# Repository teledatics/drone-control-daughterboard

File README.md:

# Drone Control

This is a hardware add-on 'lid' for the kimχ micro that adds drone control hardware
replacing a separate PX4 external embedded subsystem. The kimχ micro with the drone-
control add-on board is an all-in-one embedded drone and rover control system.

The kimχ micro with the drone-control add-on is an [i.MX8M Mini](https://www.nxp.com/products/processors-and-microcontrollers/arm-processors/i-mx-applications-processors/i-mx-8-applications-processors/i-mx-8m-mini-arm-cortex-a53-cortex-m4-audio-voice-video:i.MX8MMINI) Linux system with a 
32mm x 65mm x 10mm form factor.

## kimχ micro

kimχ micro is a small and spicy open hardware embedded SBC that offers tons of
versitility for many different applications.

[kimχ micro](https://github.com/groupgets/kimchi-micro)

## Features

* m.2 connector for [NXP IW612](https://www.nxp.com/products/wireless/wi-fi-plus-bluetooth-plus-802-15-4/2-4-5-ghz-dual-band-1x1-wi-fi-6-802-11ax-plus-bluetooth-5-2-plus-802-15-4-tri-radio-solution:IW612) Wi-Fi 6E/Bluetooth & BLE/Zigbee 802.15.4 board
* Gigabit Ethernet port
* ST Micro [ISM330DHCX](https://www.st.com/en/mems-and-sensors/ism330dhcx.html) IMU gyroscope/accelerometer
* ST Micro [IIS2MDC](https://www.st.com/en/mems-and-sensors/iis2mdc.html) magnetometer/compass
* Bosch [BMP581](https://www.bosch-sensortec.com/products/environmental-sensors/pressure-sensors/bmp581/) pressure sensor for altitude
* 15-pin Connector for Raspberry Pi v2 HD camera
* GPS & Telemetry connectors for NXP drone & rover kits
* PWM control for up to 8 external motors w/ NXP rover & drone kit compatible connector

## Work In Progress

Stay tuned for updates to both the hardware and software as we add features and port
PX4 Autopilot to the i.MX8M Mini on-board embedded ARM m4 core

Please see our Drone Control Yocto github repository to build a Linux OS for the kimχ 
micro with drone-control daughterboard

[Drone Control Yocto](https://github.com/teledatics/drone-control-yocto)

## Drone Control Components

The Drone Control components for a complete system.

* kimχ micro i.MX8M Mini SBC
* drone control add-on board
* NXP IW612 Wi-Fi/BT/802.15.4 m.2 card
* Teledatics 802.11ah HaLow long range mini-PCIe Wi-Fi card
* Raspberry Pi v2 camera

## Assembled Ready To Fly

32mm x 65mm x 15mm assembled drone control kit ready to mount on an NXP drone or rover kit.

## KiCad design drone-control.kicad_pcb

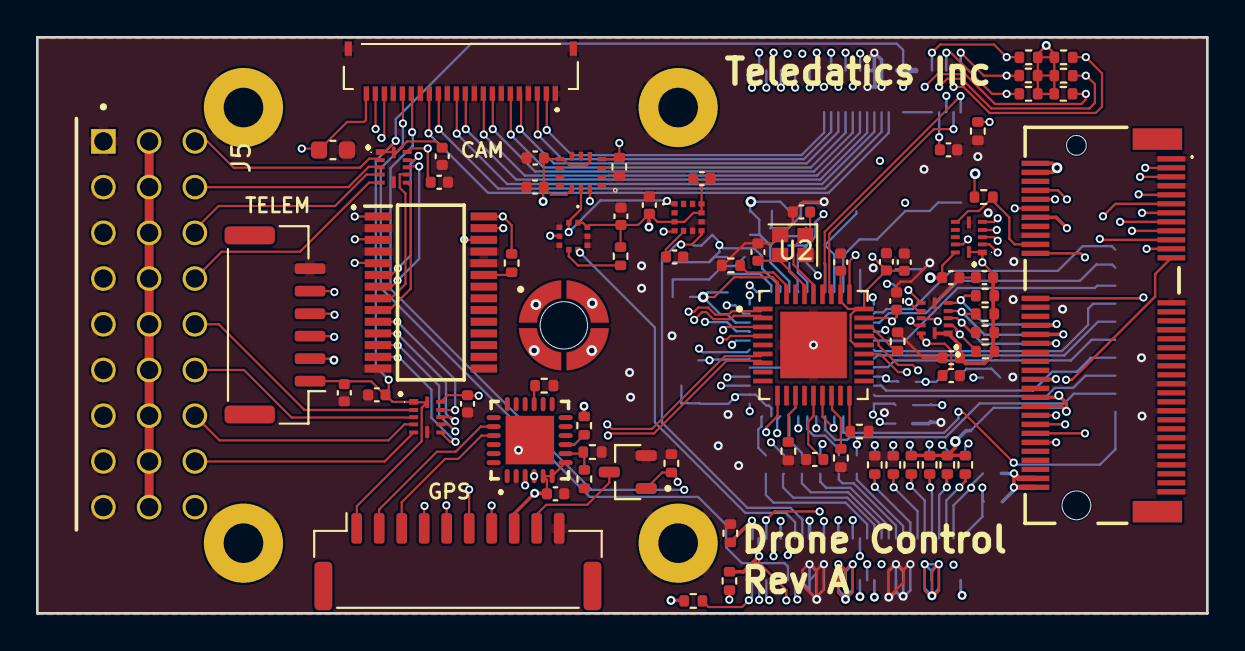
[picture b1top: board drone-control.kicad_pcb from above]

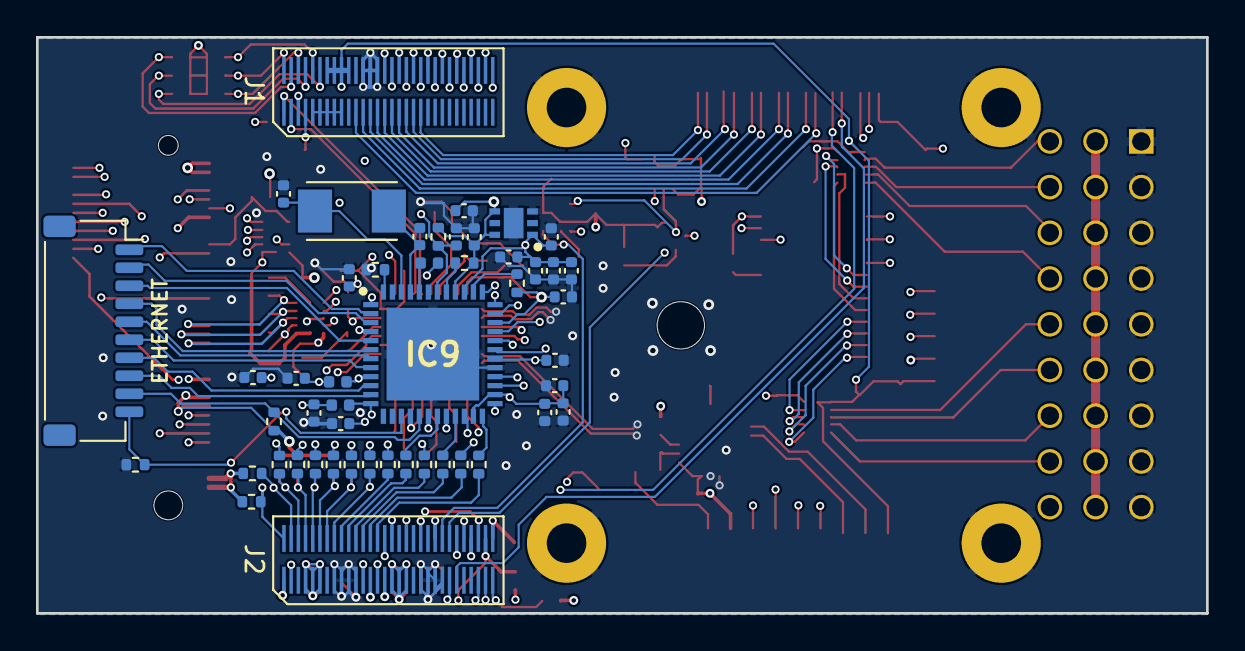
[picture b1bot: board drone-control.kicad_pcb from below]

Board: 6 copper layers, 65.0 x 32.0 mm, 131 parts (54 on the bottom side), 153 nets.

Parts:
C1, C2, C3, C4, C6, C7, C8, C9, C12, C13, C14, C17, C19, C20, C21, C27, C28, C29, C30, C31, C32, C33, C34, C35, C36, C37, C38, C40, C41, C42, C43: 100n; C_0402_1005Metric
C5: 4.7uF X5R 6.3V; C_0603_1608Metric
C10, C25, C26: 1u; C_0402_1005Metric
C11, C47, C53: 1uF; C_0402_1005Metric
C15, C16: 18pf; C_0402_1005Metric
C18: 220pf; C_0402_1005Metric
C22: 22u; C_0402_1005Metric
C23, C24: 18p; C_0402_1005Metric
C39: 4.7u; C_0402_1005Metric
FB1, FB2, FB3: 100MHz; L_0402_1005Metric
G1: teledatics_logo; teledatics_logo_kicad_footprint
H1, H2, H3, H4: MountingHole_Pad; MountingHole_2.2mm_M2_Pad
IC1, IC2, IC4, IC5: NTS0104GU12,115; NTS0104GU12115
IC3: PCA9685PW,112; SOP65P640X110-28N
IC6: ISM330DHCXTR; LGA-14_2.5X3X0.86_
IC7: IIS2MDCTR
IC8: CP2102N-A02-GQFN24R; QFN-24_L4.0-W4.0-P0.50-TL-EP2.6
IC9: KSZ9131RNXC; QFN50P700X700X90-49N
IC10: TLV75712PDRVR; SON65P200X200X80-7N
J1, J2: DF40HC(3.5)-60DS
J3: Bus_M.2_Socket_E; MDT420E03001
J5: TSW-109-08-T-T-RA; SAMTEC_TSW-109-08-T-T-RA
J6: GPS_EXT; JST_GH_SM10B-GHS-TB_1x10-1MP_P1.25mm_Horizontal
J7: Telem; JST_GH_BM06B-GHS-TBT_1x06-1MP_P1.25mm_Vertical
J8: Ethernet_Conn; JST_SH_SM10B-SRSS-TB_1x10-1MP_P1.00mm_Horizontal
J9: FH19SC-22S-0.5SH_09_; FH19SC22S05SH09
MP1: M.2 Standoff; JAE_SM3ZS067U410-NUT1-R1200
Q1: DMN3042L-7; SOT91P240X110-3N
R1, R4, R5, R6, R7, R13, R18, R19, R21, R26, R27, R28, R33: 100K; R_0402_1005Metric
R2, R3, R8, R9, R10, R11, R12, R16, R31, R46, R47, R48, R49, R52, R56, R57: 10K; R_0402_1005Metric
R14, R25, R50, R51, R53, R54, R55: 1K; R_0402_1005Metric
R15: 6.04K 1%; R_0402_1005Metric
R17: 47K; R_0402_1005Metric
R20: 4K7; R_0402_1005Metric
R22: 2K; R_0402_1005Metric
R23: 22K; R_0402_1005Metric
R24, R35, R36, R37, R38, R39, R40, R41, R42, R43, R44, R45: 22R; R_0402_1005Metric
R29: 12K 1%; R_0402_1005Metric
U1: BMP581
U2: USB2533I-1080AEN; QFN50P600X600X100-37N
Y1: ABM3-25.000MHZ-D2Y-T; XTAL_ABM3-25.000MHZ-D2Y-T
Y2: 24 MHz; Crystal_SMD_2016-4Pin_2.0x1.6mm

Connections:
/CAM_CK_N: J1.45, J9.8
/CAM_CK_P: J1.46, J9.9
/CAM_D0_N: J1.41, J9.2
/CAM_D0_P: J1.42, J9.3
/CAM_D1_N: J1.43, J9.5
/CAM_D1_P: J1.44, J9.6
/CAM_D2_N: J1.47, J9.11
/CAM_D2_P: J1.48, J9.12
/CAM_D3_N: J1.49, J9.14
/CAM_D3_P: J1.50, J9.15
/Connectors/BUZZER: J6.9, Q1.3
/ENET_MDC: IC9.36 (MDC), J2.2, R25.1
/ENET_MDIO: IC9.37 (MDIO), J2.1, R14.1
/ENET_RD0: J2.6, R36.2, R46.1
/ENET_RD1: J2.4, R37.2, R47.1
/ENET_RD2: J2.5, R38.2, R48.1
/ENET_RD3: J2.3, R39.2, R49.1
/ENET_RXC: J2.7, R24.2, R50.2
/ENET_RX_CTL: J2.8, R35.2, R51.2
/ENET_TD0: J2.10, R41.2
/ENET_TD1: J2.9, R42.2
/ENET_TD2: J2.12, R43.2
/ENET_TD3: J2.11, R44.2
/ENET_TXC: J2.14, R45.2
/ENET_TX_CTL: J2.13, R40.2
/Ethernet/AVDDH: FB1.1, IC9.1 (AVDDH_1), IC9.12 (AVDDH_2)
/Ethernet/AVDDL: FB2.1, IC9.4 (AVDDL_1), IC9.9 (AVDDL_2)
/Ethernet/AVDPLL: FB3.1, IC9.44 (AVDDL_PLL)
/Ethernet/LED1: IC9.17 (LED1/PME_N1//PHYAD0), J8.9, R53.1
/Ethernet/LED2: IC9.15 (LED2/PHYAD1), J8.10, R54.1
/Ethernet/TRD1+: IC9.2 (TXRXP_A), J8.1
/Ethernet/TRD1-: IC9.3 (TXRXM_A), J8.2
/Ethernet/TRD2+: IC9.5 (TXRXP_B), J8.3
/Ethernet/TRD2-: IC9.6 (TXRXM_B), J8.4
/Ethernet/TRD3+: IC9.7 (TXRXP_C), J8.5
/Ethernet/TRD3-: IC9.8 (TXRXM_C), J8.6
/Ethernet/TRD4+: IC9.10 (TXRXP_D), J8.7
/Ethernet/TRD4-: IC9.11 (TXRXM_D), J8.8
/USB2_ID: J1.58, R28.2
/USDHC3_CLK: J1.2, J3.9 (SDIO_CLK), R4.1
/USDHC3_CMD: J1.1, J3.11 (SDIO_CMD), R5.1
/USDHC3_DATA0: J1.4, J3.13 (SDIO_DATA0), R6.1
/USDHC3_DATA1: J1.5, J3.15 (SDIO_DATA1), R7.1
/USDHC3_DATA2: J1.6, J3.17 (SDIO_DATA2), R26.1
/USDHC3_DATA3: J1.3, J3.19 (SDIO_DATA3), R27.1
BEC: J5.02, J5.05, J5.08, J5.11, J5.14, J5.17, J5.20, J5.23, J5.26
BT_WAKE_3V3: IC2.7 (B4), J3.20 (~UART_WAKE), R3.1
ECSPI2_MISO: IC1.8 (B3), J1.30
ECSPI2_MISO_1V8: IC1.4 (A3), J3.40 (VENDOR_DEFINED), R8.1
ECSPI2_MOSI: IC1.7 (B4), J1.29
ECSPI2_MOSI_1V8: IC1.5 (A4), J3.38 (VENDOR_DEFINED), R9.1
ECSPI2_SCLK: IC1.9 (B2), J1.27
ECSPI2_SCLK_1V8: IC1.3 (A2), J3.42 (VENDOR_DEFINED), R11.1
ECSPI2_SS0: IC1.10 (B1), J1.28
ECSPI2_SS0_1V8: IC1.2 (A1), J3.64 (RESERVED), R10.1
GND: C1.2, C2.2, C3.2, C4.2, C5.2, C6.2, C7.2, C8.2, C9.2, C10.1, C11.2, C12.2, C13.2, C14.1, C15.1, C16.1, C17.2, C18.2, C19.2, C20.2, C21.2, C22.1, C23.2, C24.2, C25.2, C26.2, C27.2, C28.2, C29.2, C30.2, C31.2, C32.2, C33.2, C34.2, C35.2, C36.2, C37.2, C38.2, C39.2, C40.2, C41.2, C42.2, C43.1, C47.2, C53.1, H1.1, H2.1, H3.1, H4.1, IC1.6 (GND), IC2.6 (GND), IC3.2 (A1), IC3.4 (A3), IC3.14 (VSS), IC3.24 (A5), IC3.25 (EXTCLK), IC4.6 (GND), IC5.6 (GND), IC6.6 (GND_1), IC6.7 (GND_2), IC7.6 (GND_1), IC7.8 (GND_2), IC8.2 (GND), IC8.25 (EPAD), IC9.29 (VSS), IC9.49 (P_VSS), IC10.3 (GND_1), IC10.7 (GND_2), J1.12, J1.13, J1.14, J2.38, J2.39, J2.40, J2.41, J2.50, J2.51, J2.52, J2.53, J3.1 (GND), J3.7 (GND), J3.18 (GND), J3.33 (GND), J3.34 (UART_CTS), J3.39 (GND), J3.45 (GND), J3.51 (GND), J3.57 (GND), J3.63 (GND), J3.69 (GND), J3.75 (GND), J5.01, J5.04, J5.07, J5.10, J5.13, J5.16, J5.19, J5.22, J5.25, J6.10, J7.6, J9.1, J9.4, J9.7, J9.10, J9.13, J9.16, J9.19, J9.MP1 (MH1), J9.MP2 (MH2), MP1.1, MP1.2, MP1.3, MP1.4, Q1.2, R1.2, R13.1, R15.1, R16.2, R17.2, R18.1, R19.1, R20.1, R28.1, R29.1, R33.1, R50.1, R51.1, R54.2, R57.2, U1.3 (VSS_1), U1.5 (SDO), U1.8 (VSS_2), U1.9 (VSS_3), U2.37 (VSS), Y2.2, Y2.4
GPIO1_01: J2.29, J3.21 (~SDIO_WAKE), R2.1
GPIO1_09: J2.28, J3.23 (~SDIO_RESET)
GPIO1_10: J2.27, J3.62 (~ALERT)
GPIO1_11: IC2.5 (A4), J2.26
GPIO1_12: J2.25, Q1.1, R57.1
GPIO1_13: J2.24, U1.7 (INT)
GPIO1_14: IC7.7 (INT/DRDY), J2.23
GPIO1_15: IC6.4 (INT1), J2.22, R20.2
GPIO5_06: J1.23, J6.6
GPIO5_07: J1.25, J6.7
GPS_RXD: IC8.21 (TXD), J6.3
GPS_TXD: IC8.20 (RXD), J6.2
GPS_USB_N: IC8.4 (D-), U2.6 (USBDN3_DM/~PRT_DIS_M3)
GPS_USB_P: IC8.3 (D+), U2.7 (USBDN3_DP/~PRT_DIS_P3)
I2C1_SCL: IC6.13 (SCL), IC7.1 (SCL/SPC), J1.22, U1.2 (SCK)
I2C1_SDA: IC6.14 (SDA), IC7.4 (SDA/SDI/SDO), J1.21, U1.4 (SDI)
I2C2_SCL: J1.20, J3.60 (I2C_CLK)
I2C2_SDA: J1.19, J3.58 (I2C_DATA)
I2C3_SCL: IC3.26 (SCL), J1.18, J9.20
I2C3_SDA: IC3.27 (SDA), J1.17, J9.21
I2C4_SCL: J1.16, J6.4, U2.24 (SCL/SMBCLK/~CFG_SEL0)
I2C4_SDA: J1.15, J6.5, U2.22 (SDA/SMBDATA/~NON_REM1)
M2_USB_N: J3.5 (USB_D-), U2.3 (USBDN2_DM/~PRT_DIS_M2)
M2_USB_P: J3.3 (USB_D+), U2.4 (USBDN2_DP/~PRT_DIS_P2)
unnamed: IC3.23 (~OE), R12.1
unnamed: C18.1, IC7.5 (C1)
unnamed: IC8.9 (RSTB), R22.2
unnamed: IC8.15 (SUSPENDB), R16.1
unnamed: IC8.8 (VBUS), R17.1, R23.2
unnamed: IC9.41 (CLK125_NDO/LED_MODE), R52.1
unnamed: IC9.38 (INT_N/PME_N2/ALLPHYAD), R56.1
unnamed: IC9.48 (ISET), R15.2
unnamed: IC9.35 (RXC/PHYAD2), R24.1
unnamed: IC9.32 (RXD0/MODE0), R36.1
unnamed: IC9.31 (RXD1/MODE1), R37.1
unnamed: IC9.28 (RXD2/MODE2), R38.1
unnamed: IC9.27 (RXD3/MODE3), R39.1
unnamed: IC9.33 (RX_CTL/CLK125_EN), R35.1
unnamed: IC9.24 (TXC), R45.1
unnamed: IC9.19 (TXD0), R41.1
unnamed: IC9.20 (TXD1), R42.1
unnamed: IC9.21 (TXD2), R43.1
unnamed: IC9.22 (TXD3), R44.1
unnamed: IC9.25 (TX_CTL), R40.1
unnamed: C23.1, IC9.46 (XI), Y1.1
unnamed: C24.1, IC9.45 (XO), Y1.2
unnamed: R21.1, U1.6 (CSB)
unnamed: R33.2, U2.25 (HS_IND/~CFG_SEL1)
unnamed: R13.2, U2.12 (PRTPWR1/PRTCTL1/~BC_EN1)
unnamed: R18.2, U2.16 (PRTPWR2/PRTCTL2/~BC_EN2)
unnamed: R19.2, U2.18 (PRTPWR3/PRTCTL3/~BC_EN3)
unnamed: R29.2, U2.35 (RBIAS)
unnamed: C10.2, U2.14 (VDDCR12)
unnamed: C16.2, U2.33 (XTAL1/REFCLK), Y2.3
unnamed: C15.2, U2.32 (XTAL2), Y2.1
PCIE_USB_D_N: J2.60, U2.1 (SWAP_USBDN1_DM/~PRT_DIS_M1)
PCIE_USB_D_P: J2.59, U2.2 (SWAP_USBDN1_DP/~PRT_DIS_P1)
PWM0_3v3: IC3.6 (LED0), IC4.10 (B1)
PWM0_5v: IC4.2 (A1), J5.03
PWM1_3v3: IC3.7 (LED1), IC4.9 (B2)
PWM1_5v: IC4.3 (A2), J5.06
PWM2_3v3: IC3.8 (LED2), IC4.8 (B3)
PWM2_5v: IC4.4 (A3), J5.09
PWM3_3v3: IC3.9 (LED3), IC4.7 (B4)
PWM3_5v: IC4.5 (A4), J5.12
PWM4_3v3: IC3.10 (LED4), IC5.10 (B1)
PWM4_5v: IC5.2 (A1), J5.15
PWM5_3v3: IC3.11 (LED5), IC5.9 (B2)
PWM5_5v: IC5.3 (A2), J5.18
PWM6_3v3: IC3.12 (LED6), IC5.8 (B3)
PWM6_5v: IC5.4 (A3), J5.21
PWM7_3v3: IC3.13 (LED7), IC5.7 (B4)
PWM7_5v: IC5.5 (A4), J5.24
REF_CLK_32KHz_3V3: IC2.10 (B1), J3.50 (SUSCLK)
REF_CLK_32KHz_GPIO01_00: IC2.2 (A1), J2.30, R1.1
SAI2_MCLK: J2.20, J3.8 (PCM_CLK/I2S_SCK)
SAI2_RXD0: J2.15, J3.14 (PCM_OUT/I2S_SD_OUT)
SAI2_TXD0: J2.18, J3.12 (PCM_IN/I2S_SD_IN)
SAI2_TXFS: J2.16, J3.10 (PCM_SYNC/I2S_WS)
SAI3_MCLK: J2.37, J9.17
SAI3_RXD: J2.33, U2.28 (SUSP_IND/LOCAL_PWR/~NON_REM0)
SAI3_TXC: C53.2, J2.31, R31.2, U2.26 (~RESET)
SAI3_TXD: C42.1, IC9.42 (RESET_N), J2.32, R55.1
SAI3_TXFS: J2.36, J9.18
UART1_RX: J2.47, J3.22 (UART_RXD)
UART1_TX: J2.46, J3.32 (UART_TXD)
UART3_CTS: J1.26, J7.4
UART3_RTS: J1.24, J7.5
UART3_RX: IC2.4 (A3), J2.49, J7.3
UART3_TX: IC2.3 (A2), J2.48, J7.2
USB2_DN: J1.59, U2.30 (FLEX_USBUP_DM)
USB2_DP: J1.60, U2.31 (FLEX_USBUP_DP)
VCHG: J1.52, J1.53, J1.54, J1.55, J1.56
VDD_1V8: C1.1, C2.1, C14.2, C17.1, C19.1, C20.1, C21.1, IC1.1 (VCC(A)), IC1.12 (OE), IC2.1 (VCC(A)), IC2.12 (OE), IC6.5 (VDDIO), IC6.8 (VDD), IC6.12 (CS), IC7.3 (CS), IC7.9 (VDD), IC7.10 (VDD_IO), J2.43, J2.44, J2.45, R2.2, R4.2, R5.2, R6.2, R7.2, R8.2, R9.2, R10.2, R11.2, R21.2, R26.2, R27.2, U1.1 (VDDIO), U1.10 (VDD)
VDD_3V3: C3.1, C4.1, C5.1, C7.1, C9.1, C11.1, C12.1, C13.1, C22.2, C25.1, C32.1, C33.1, C34.1, IC1.11 (VCC(B)), IC2.11 (VCC(B)), IC3.1 (A0), IC3.3 (A2), IC3.5 (A4), IC3.28 (VDD), IC4.11 (VCC(B)), IC5.11 (VCC(B)), IC8.5 (VIO), IC8.6 (VDD), IC8.7 (VREGIN), IC9.16 (DVDDH_1), IC9.34 (DVDDH_2), IC9.40 (DVDDH_3), IC10.4 (EN), IC10.6 (IN), J2.55, J2.56, J2.57, J3.2 (3.3V), J3.4 (3.3V), J3.54 (~W_DISABLE2), J3.56 (~W_DISABLE1), J3.72 (3.3V), J3.74 (3.3V), J6.8, J9.22, R3.2, R12.2, R14.2, R22.1, R25.2, R31.1, R46.2, R47.2, R48.2, R49.2, R52.2, R53.2, R55.2, R56.2, U2.10 (VDDA33), U2.15 (VDD33), U2.23 (VDD33), U2.27 (VBUS_DET/PIO16), U2.29 (VDDA33), U2.36 (VDDA33)
VDD_5V: C6.1, C8.1, C43.2, C47.1, IC4.1 (VCC(A)), IC4.12 (OE), IC5.1 (VCC(A)), IC5.12 (OE), J1.7, J1.8, J1.9, J1.10, J1.57, J6.1, J7.1
VDD_PHY_1V2: C26.1, C27.1, C28.1, C29.1, C30.1, C31.1, C35.1, C36.1, C37.1, C38.1, C39.1, C40.1, C41.1, FB1.2, FB2.2, FB3.2, IC9.18 (DVDDL_1), IC9.23 (DVDDL_2), IC9.26 (DVDDL_3), IC9.30 (DVDDL_4), IC9.39 (DVDDL_5), IC10.1 (OUT)

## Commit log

2023-03-31 move silkscreen to fab
2023-03-31 fix typo
2023-03-31 add links
2023-03-31 add form factor
2023-03-31 add images of components and assmbled system
2023-03-31 add RPi camera
